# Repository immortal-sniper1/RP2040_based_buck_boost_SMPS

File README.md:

# RP2040_based_buck_boost_SMPS
 A test build where i want to use a RP2040 MCU in order to controll a SMPS with a buck-boost topology. That is also syncronous in nature. As of now i am not sure how fast it can run and what are the absolute maximum operation parameters. Also I will try to make this project run with FreeRTOS or use PIO in order to free the un used pins for other uses.

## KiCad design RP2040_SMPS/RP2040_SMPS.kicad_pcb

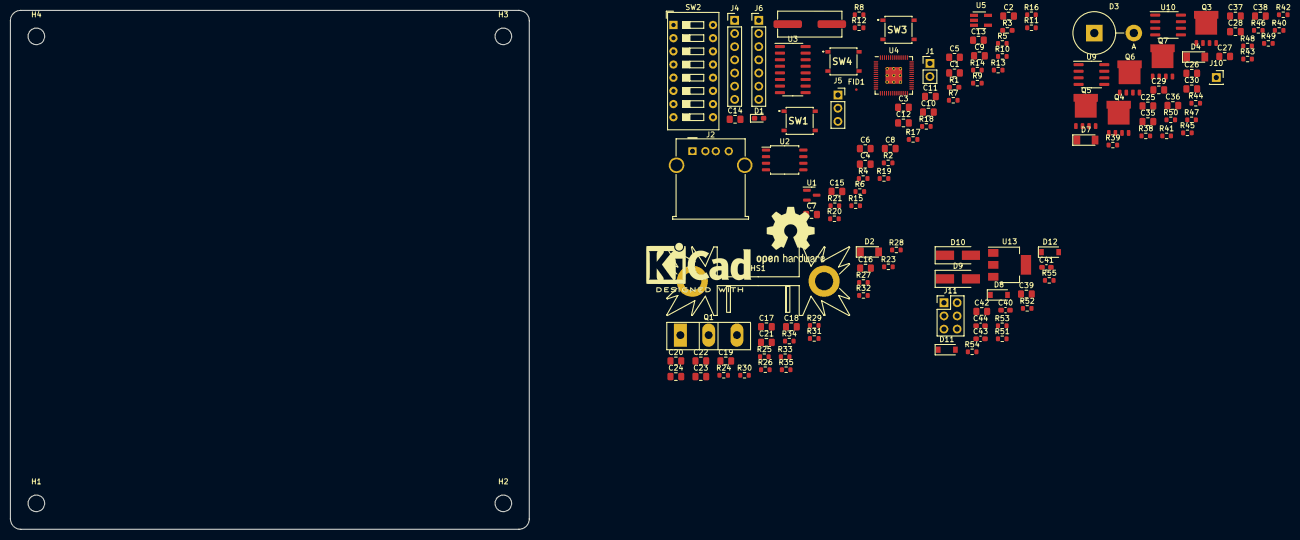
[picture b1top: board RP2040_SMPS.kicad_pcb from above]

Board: 2 copper layers, 100.0 x 100.0 mm, 136 parts (0 on the bottom side), 87 nets, no tracks yet.

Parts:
C1, C2, C3, C4, C5, C6, C7, C8, C9, C10, C11, C12, C15, C20, C21, C22, C23, C24, C35, C36, C37, C38, C39, C42: 100n; C_0805_2012Metric_Pad1.18x1.45mm_HandSolder
C13, C14: DNP; C_0805_2012Metric_Pad1.18x1.45mm_HandSolder
C16, C17, C18, C19, C25, C26, C27, C28, C29, C30: 10u@50V; C_0805_2012Metric_Pad1.18x1.45mm_HandSolder
C40, C41, C43, C44: 10u; C_0603_1608Metric_Pad1.08x0.95mm_HandSolder
D1: LED_Small Red; LED_0603_1608Metric_Pad1.05x0.95mm_HandSolder
D2, D4, D7: ZMM3V3-M; D_MiniMELF
D3: 18v; D_5KPW_P7.62mm_Vertical_AnodeUp
D8, D11, D12: B5819W_SL; D_SOD-123
D9, D10: SS210; D_SMA_Handsoldering
FID1: Fiducial; Fiducial_0.5mm_Mask1mm
FID2: Fiducial; KiCad-Logo2_8mm_SilkScreen
FID3: Fiducial; OSHW-Logo2_14.6x12mm_SilkScreen
H1, H2, H3, H4: MountingHole; MountingHole_3.2mm_M3
HS1: Heatsink_Pad_2Pin; HSE-B20500-040H
J1: Conn_01x02; PinHeader_1x02_P2.54mm_Vertical
J2: USB_B_Mini; USB_A_Molex_67643_Horizontal
J4, J6: Conn_01x07; PinHeader_1x07_P2.54mm_Vertical
J5: debug; PinSocket_1x03_P2.54mm_Vertical
J10: Conn_01x01; PinSocket_1x01_P2.54mm_Vertical
J11: jumper; PinHeader_2x03_P2.54mm_Vertical
Q1: Q_PMOS_DGS; TO-247-3_Vertical
Q3, Q4, Q5, Q6, Q7: HYG025N06LS1C2; DFN-8_(5x6)
R1: 330; R_0603_1608Metric_Pad0.98x0.95mm_HandSolder
R2, R4, R8, R25, R32, R33, R34, R35, R38, R47, R48, R49, R50, R51: 1k; R_0603_1608Metric
R3: DNF; R_0603_1608Metric_Pad0.98x0.95mm_HandSolder
R5, R6, R43, R44, R45, R46: 27; R_0603_1608Metric
R7, R23, R39, R40: 220k; R_0603_1608Metric
R9, R10, R12, R13, R14, R15, R16, R17, R18, R19, R26, R27, R28, R29, R41, R42, R54, R55: 10k; R_0603_1608Metric
R11, R20, R21: 5k6; R_0603_1608Metric
R24, R30, R31, R52, R53: 100k; R_0603_1608Metric
SW1, SW3, SW4: SW_SPST; PTS526SK15SMTR2LFS
SW2: SW_DIP_x08; SW_DIP_SPSTx08_Slide_9.78x22.5mm_W7.62mm_P2.54mm
U1: LM4040DBZ-3.0; SOT-23
U2: W25Q128JVS; SOIC-8_5.23x5.23mm_P1.27mm
U3: MC74VHC4052DR2G; SOIC-16_3.9x9.9mm_P1.27mm
U4: RP2040; RP2040-QFN-56
U5: D1213A-02SM; SOT-23-5_HandSoldering
U9, U10: LM5109BMA; SOIC-8_3.9x4.9mm_P1.27mm
U13: AMS1117-3.3; SOT-223-3_TabPin2
Y1: ABLS-12.000MHZ-B4-T; ATS120SM

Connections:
+1V1: C2.1, C3.1, C12.1, J6.7, U4.23 (DVDD), U4.45 (VREG_VOUT), U4.50 (DVDD)
+3V3: C1.1, C4.1, C5.1, C6.1, C7.1, C8.1, C9.1, C10.1, C40.1, J4.7, J6.6, R2.1, R3.1, R7.2, R9.2, R18.2, R19.2, R20.2, R21.2, SW2.11, SW2.12, SW2.13, SW2.14, SW2.15, SW2.16, U2.8 (VCC), U3.16 (VCC), U4.1 (IOVDD), U4.10 (IOVDD), U4.22 (IOVDD), U4.33 (IOVDD), U4.42 (IOVDD), U4.44 (VREG_IN), U4.48 (USB_VDD), U4.49 (IOVDD), U13.2 (VO)
+15V: U9.1 (VDD), U10.1 (VDD)
-VDC: C43.1, C44.1, D11.2 (A), R53.1, U3.7 (VEE)
/Button_down: R18.1, SW3.2 (B), U4.27 (GPIO16)
/Button_up: R19.1, SW4.2 (B), U4.28 (GPIO17)
/GPIO0: R17.2, SW2.1, U4.2 (GPIO0)
/GPIO1: R16.2, SW2.2, U4.3 (GPIO1)
/GPIO2: R15.2, SW2.3, U4.4 (GPIO2)
/GPIO3: R14.2, SW2.4, U4.5 (GPIO3)
/GPIO4: R13.2, SW2.5, U4.6 (GPIO4)
/GPIO5: R12.2, SW2.6, U4.7 (GPIO5)
/GPIO23: R7.1, U3.6 (ENABLE), U4.35 (GPIO23)
/GPIO24: U3.9 (B), U4.36 (GPIO24)
/GPIO25: R1.2, U3.10 (A), U4.37 (GPIO25)
/GPIO25-led: D1.2 (A), R1.1
/GPIO28_ADC2: U3.3 (Y), U4.40 (GPIO28_ADC2)
/GPIO29_ADC3: U3.13 (X), U4.41 (GPIO29_ADC3)
/LDO/output_LDO: D2.1 (K), R23.1, R29.2
/QSPI_SCLK: U2.6 (CLK), U4.52 (QSPI_SCLK)
/QSPI_SD0: U2.5 (DI(IO0)), U4.53 (QSPI_SD0)
/QSPI_SD1: U2.2 (DO(IO1)), U4.55 (QSPI_SD1)
/QSPI_SD2: U2.3 (IO2), U4.54 (QSPI_SD2)
/QSPI_SD3: U2.7 (IO3), U4.51 (QSPI_SD3)
/QSPI_SS: R3.2, R4.1, U2.1 (~CS), U4.56 (QSPI_SS)
/RUN: C15.1, R9.1, SW1.2 (B), SW2.10, U4.26 (RUN)
/SMPS/input: D4.1 (K), R39.1, R41.1
/SMPS/output: D7.1 (K), R40.1, R42.2
/SWCLK: J5.1, U4.24 (SWCLK)
/SWD: J5.3, U4.25 (SWD)
/USB+: R5.1, U4.47 (USB_DP)
/USB-: R6.1, U4.46 (USB_DM)
/USB_V: R10.1, R11.2, U3.15 (X2)
/V_ADC: C11.1, J6.5, R2.2, U1.1 (K), U4.43 (ADC_AVDD)
/XIN: C13.2, U4.20 (XIN), Y1.1
/XOUT: R8.1, U4.21 (XOUT)
/XOUT-raw: C14.2, R8.2, Y1.2
/~USB_BOOT: J1.1, R4.2, SW2.9
D+: J2.3 (D+), R5.2, U5.4 (CH2)
D-: J2.2 (D-), R6.2, U5.3 (CH1)
GND: C1.2, C2.2, C3.2, C4.2, C5.2, C6.2, C7.2, C8.2, C9.2, C10.2, C11.2, C12.2, C13.1, C14.1, C15.2, C16.2, C17.2, C18.2, C19.2, C20.2, C21.2, C22.2, C23.2, C24.2, C25.2, C26.2, C27.2, C28.2, C29.2, C30.2, C35.2, C36.2, C37.2, C38.2, C39.2, C40.2, C42.2, C43.2, C44.2, D1.1 (K), D2.2 (A), D3.2 (A), D4.2 (A), D7.2 (A), D12.1 (K), HS1.1, J1.2, J2.5 (GND), J4.1, J4.6, J5.2, J6.1, J6.4, J10.1, Q3.2 (S), Q6.2 (S), Q7.2 (S), R11.1, R12.1, R13.1, R14.1, R15.1, R16.1, R17.1, R28.1, R29.1, R31.2, R41.2, R42.1, R52.2, R53.2, R55.1, SW1.1 (A), SW2.7, SW2.8, SW3.1 (A), SW4.1 (A), U1.2 (A), U2.4 (GND), U3.8 (GND), U4.19 (TESTEN), U4.57 (GND), U5.2 (VSS), U9.4 (VSS), U10.4 (VSS), U13.1 (GND)
I2C_SCL: J6.2, R20.1, U4.14 (GPIO11)
I2C_SDA: J6.3, R21.1, U4.13 (GPIO10)
Input_V: D10.2 (A), R38.2
unnamed: C25.1, C30.1, R39.2
unnamed: Q4.2 (S), Q6.1 (D), U9.6 (HS)
unnamed: Q5.2 (S), Q7.1 (D), U10.6 (HS)
unnamed: C41.1, R52.1
unnamed: D3.1 (K), Q3.3 (G), R38.1
unnamed: D8.1 (K), J11.1
unnamed: D9.1 (K), J11.3
unnamed: D10.1 (K), J11.5
unnamed: C41.2, D11.1 (K), D12.2 (A)
unnamed: C18.1, C19.1, Q1.1 (D), R23.2, R24.1
unnamed: C39.1, J11.2, J11.4, J11.6, U13.3 (VI)
unnamed: C26.1, Q4.1 (D)
unnamed: C27.1, Q5.1 (D)
unnamed: C28.1, C29.1, R40.2
unnamed: C20.1, Q1.2 (G), R25.2
unnamed: C16.1, C17.1, Q1.3 (S), R27.2
unnamed: Q4.3 (G), R43.2
unnamed: Q5.3 (G), R44.1
unnamed: Q7.3 (G), R46.1
unnamed: R26.1, R31.1
unnamed: R45.1, U9.5 (LO)
unnamed: Q6.3 (G), R45.2
unnamed: C42.1, R51.1
unnamed: R51.2, R54.2
unnamed: C21.1, R32.2
unnamed: R24.2, R28.2
unnamed: C22.1, R33.2
unnamed: C23.1, R34.2
unnamed: C24.1, R35.2
unnamed: R27.1, R30.2
unnamed: C36.1, R48.1
unnamed: R43.1, U9.7 (HO)
unnamed: R46.2, U10.5 (LO)
unnamed: R44.2, U10.7 (HO)
unnamed: C35.1, R47.1
unnamed: C38.1, R50.1
unnamed: C37.1, R49.1
unnamed: R54.1, R55.2
SPI_MISO: J4.3, U4.15 (GPIO12)
SPI_MOSI: J4.4, U4.18 (GPIO15)
SPI_SCK: J4.2, U4.17 (GPIO14)
SPI_SS: J4.5, U4.16 (GPIO13)
VBUS: D8.2 (A), R10.2, U5.5 (VCC)
